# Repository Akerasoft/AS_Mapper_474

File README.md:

# AS_Mapper_474
NES compatible mapper that gives nearly 48KB instead of 32KB.  Has the linear space of NROM so no bank swapping.

Begining byte is $4020 until $FFFF.  Called NROM-383 by rounding down.
Mapper 474 submapper 0.

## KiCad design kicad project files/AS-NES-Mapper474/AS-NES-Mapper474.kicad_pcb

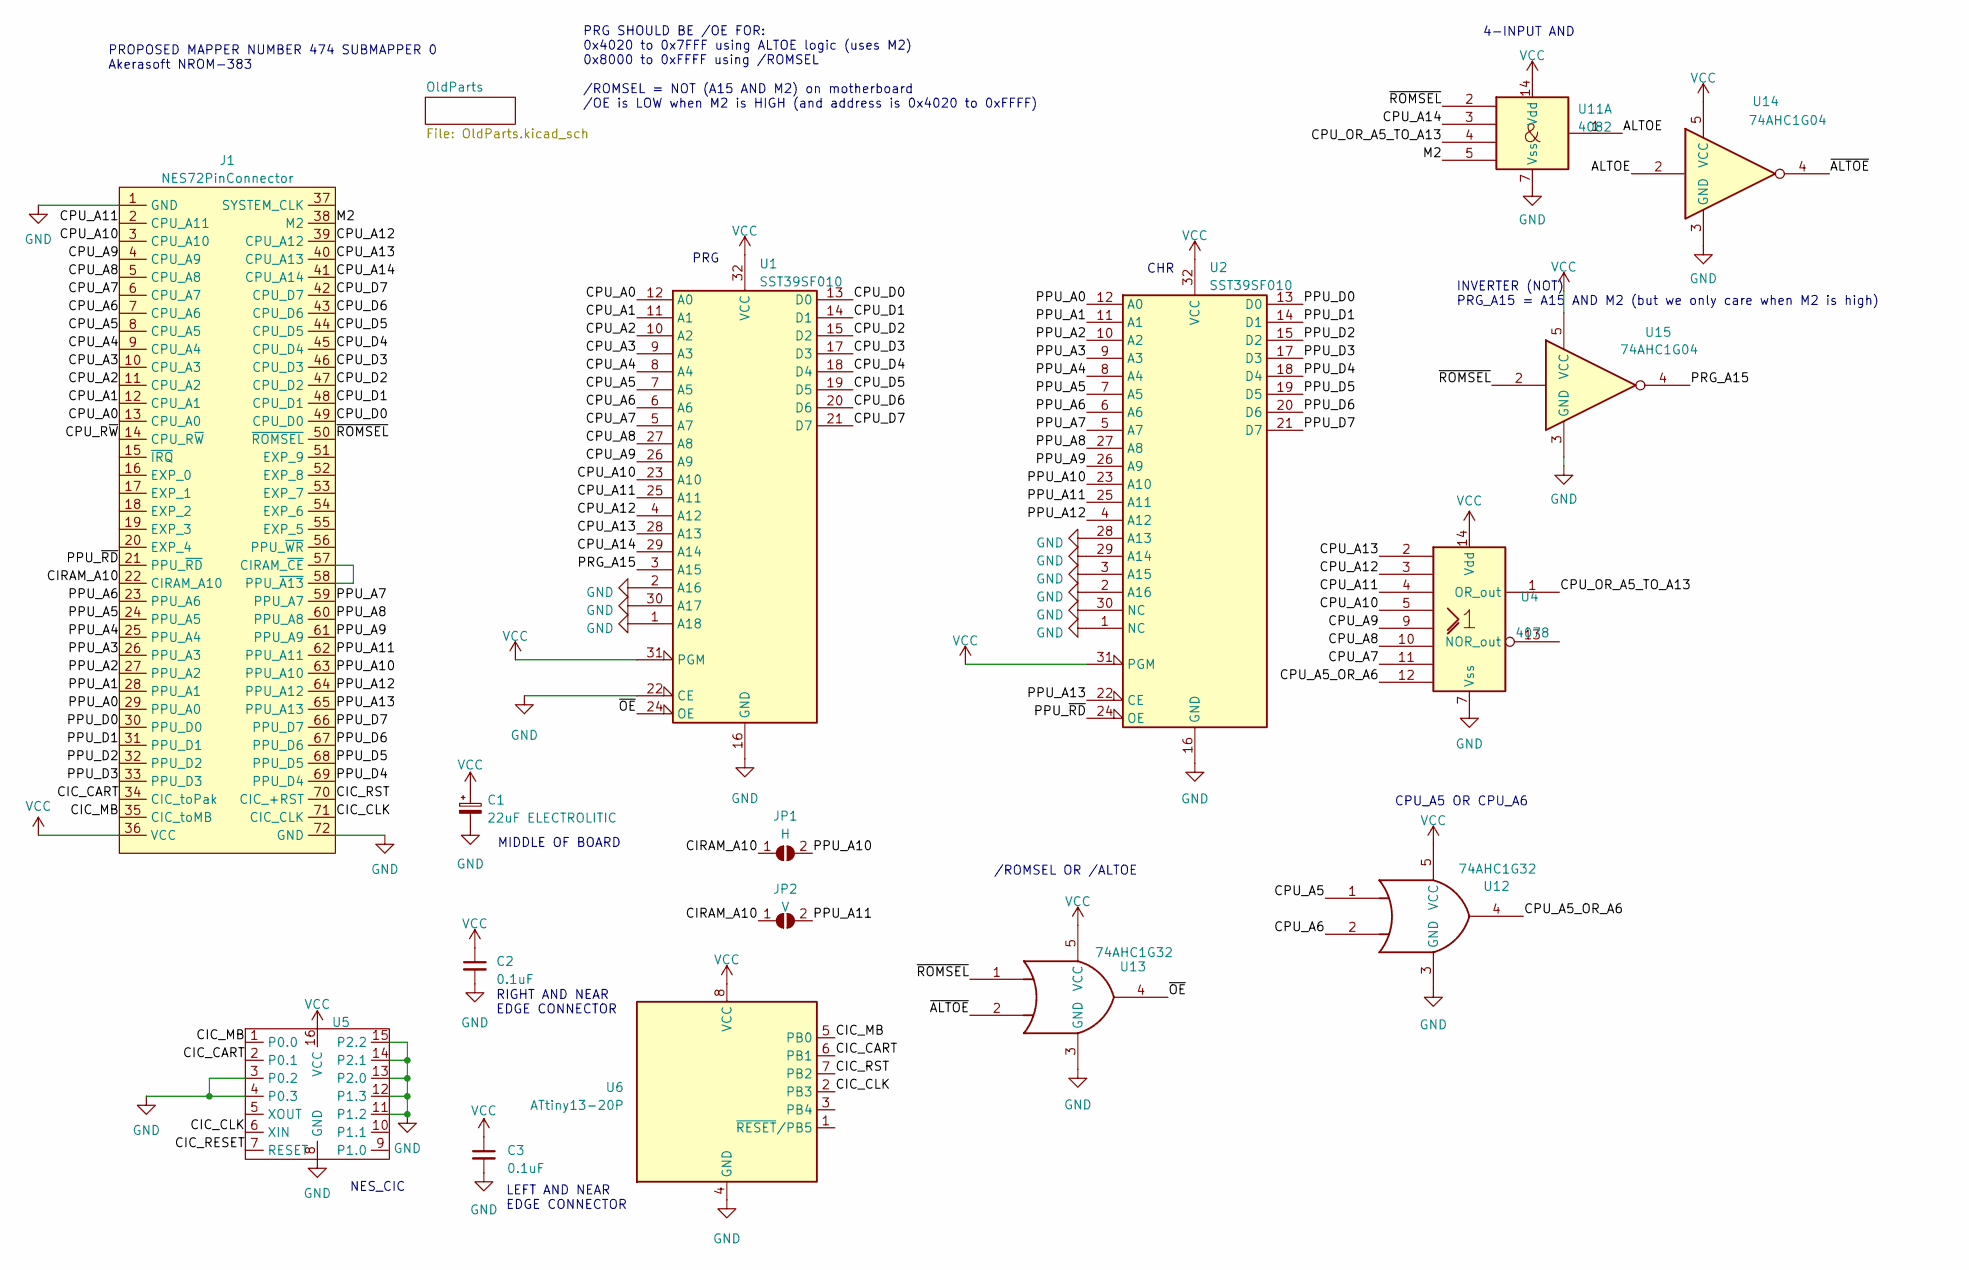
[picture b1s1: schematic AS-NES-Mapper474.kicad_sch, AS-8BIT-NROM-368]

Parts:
C1: 22uF ELECTROLITIC; CP_Radial_D5.0mm_P2.50mm
C2, C3: 0.1uF; C_Disc_D3.0mm_W1.6mm_P2.50mm
J1: NES72PinConnector; NES72PinEdgeConnector2
JP1: H; SolderJumper-2_P1.3mm_Open_Pad1.0x1.5mm
JP2: V; SolderJumper-2_P1.3mm_Open_Pad1.0x1.5mm
U1, U2: SST39SF010; DIP-32_W15.24mm
U4: 4078; DIP-14_W7.62mm
U5: DIP-16_W7.62mm
U6: ATtiny13-20P; DIP-8_W7.62mm
U11: 4082; DIP-14_W7.62mm
U12, U13: 74AHC1G32; SOT-23-5
U14, U15: 74AHC1G04; SOT-23-5

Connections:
/ALTOE: U11.1, U14.2
/CIC_CART: J1.34 (CIC_toPak), U5.2 (P0.1), U6.6 (PB1)
/CIC_CLK: J1.71 (CIC_CLK), U5.6 (XIN), U6.2 (PB3)
/CIC_MB: J1.35 (CIC_toMB), U5.1 (P0.0), U6.5 (PB0)
/CIC_RESET: U5.7 (RESET)
/CIC_RST: J1.70 (CIC_+RST), U6.7 (PB2)
/CIRAM_A10: J1.22 (CIRAM_A10), JP1.1 (A), JP2.1 (A)
/CPU_A0: J1.13 (CPU_A0), U1.12 (A0)
/CPU_A1: J1.12 (CPU_A1), U1.11 (A1)
/CPU_A2: J1.11 (CPU_A2), U1.10 (A2)
/CPU_A3: J1.10 (CPU_A3), U1.9 (A3)
/CPU_A4: J1.9 (CPU_A4), U1.8 (A4)
/CPU_A5: J1.8 (CPU_A5), U1.7 (A5), U12.1
/CPU_A5_OR_A6: U4.12, U12.4
/CPU_A6: J1.7 (CPU_A6), U1.6 (A6), U12.2
/CPU_A7: J1.6 (CPU_A7), U1.5 (A7), U4.11
/CPU_A8: J1.5 (CPU_A8), U1.27 (A8), U4.10
/CPU_A9: J1.4 (CPU_A9), U1.26 (A9), U4.9
/CPU_A10: J1.3 (CPU_A10), U1.23 (A10), U4.5
/CPU_A11: J1.2 (CPU_A11), U1.25 (A11), U4.4
/CPU_A12: J1.39 (CPU_A12), U1.4 (A12), U4.3
/CPU_A13: J1.40 (CPU_A13), U1.28 (A13), U4.2
/CPU_A14: J1.41 (CPU_A14), U1.29 (A14), U11.3
/CPU_D0: J1.49 (CPU_D0), U1.13 (D0)
/CPU_D1: J1.48 (CPU_D1), U1.14 (D1)
/CPU_D2: J1.47 (CPU_D2), U1.15 (D2)
/CPU_D3: J1.46 (CPU_D3), U1.17 (D3)
/CPU_D4: J1.45 (CPU_D4), U1.18 (D4)
/CPU_D5: J1.44 (CPU_D5), U1.19 (D5)
/CPU_D6: J1.43 (CPU_D6), U1.20 (D6)
/CPU_D7: J1.42 (CPU_D7), U1.21 (D7)
/CPU_OR_A5_TO_A13: U4.1 (OR_out), U11.4
/CPU_R~W: J1.14 (CPU_R~W)
/M2: J1.38 (M2), U11.5
/PPU_A0: J1.29 (PPU_A0), U2.12 (A0)
/PPU_A1: J1.28 (PPU_A1), U2.11 (A1)
/PPU_A2: J1.27 (PPU_A2), U2.10 (A2)
/PPU_A3: J1.26 (PPU_A3), U2.9 (A3)
/PPU_A4: J1.25 (PPU_A4), U2.8 (A4)
/PPU_A5: J1.24 (PPU_A5), U2.7 (A5)
/PPU_A6: J1.23 (PPU_A6), U2.6 (A6)
/PPU_A7: J1.59 (PPU_A7), U2.5 (A7)
/PPU_A8: J1.60 (PPU_A8), U2.27 (A8)
/PPU_A9: J1.61 (PPU_A9), U2.26 (A9)
/PPU_A10: J1.63 (PPU_A10), JP1.2 (B), U2.23 (A10)
/PPU_A11: J1.62 (PPU_A11), JP2.2 (B), U2.25 (A11)
/PPU_A12: J1.64 (PPU_A12), U2.4 (A12)
/PPU_A13: J1.65 (PPU_A13), U2.22 (CE)
/PPU_D0: J1.30 (PPU_D0), U2.13 (D0)
/PPU_D1: J1.31 (PPU_D1), U2.14 (D1)
/PPU_D2: J1.32 (PPU_D2), U2.15 (D2)
/PPU_D3: J1.33 (PPU_D3), U2.17 (D3)
/PPU_D4: J1.69 (PPU_D4), U2.18 (D4)
/PPU_D5: J1.68 (PPU_D5), U2.19 (D5)
/PPU_D6: J1.67 (PPU_D6), U2.20 (D6)
/PPU_D7: J1.66 (PPU_D7), U2.21 (D7)
/PPU_~RD: J1.21 (PPU_~RD), U2.24 (OE)
/PRG_A15: U1.3 (A15), U15.4
/~ALTOE: U13.2, U14.4
/~OE: U1.24 (OE), U13.4
/~ROMSEL: J1.50 (~ROMSEL), U11.2, U13.1, U15.2
GND: C1.2, C2.2, C3.2, J1.1 (GND), J1.72 (GND), U1.1 (A18), U1.2 (A16), U1.16 (GND), U1.22 (CE), U1.30 (A17), U2.1 (NC), U2.2 (A16), U2.3 (A15), U2.16 (GND), U2.28 (A13), U2.29 (A14), U2.30 (NC), U4.7 (Vss), U5.3 (P0.2), U5.4 (P0.3), U5.8 (GND), U5.11 (P1.2), U5.12 (P1.3), U5.13 (P2.0), U5.14 (P2.1), U5.15 (P2.2), U6.4 (GND), U11.7 (Vss), U12.3 (GND), U13.3 (GND), U14.3 (GND), U15.3 (GND)
unnamed: J1.57 (CIRAM_~CE), J1.58 (PPU_~A13)
VCC: C1.1, C2.1, C3.1, J1.36 (VCC), U1.31 (PGM), U1.32 (VCC), U2.31 (PGM), U2.32 (VCC), U4.14 (Vdd), U5.16 (VCC), U6.8 (VCC), U11.14 (Vdd), U12.5 (VCC), U13.5 (VCC), U14.5 (VCC), U15.5 (VCC)

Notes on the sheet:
PROPOSED MAPPER NUMBER 474 SUBMAPPER 0 Akerasoft NROM-383
4-INPUT AND
/ROMSEL OR /ALTOE
RIGHT AND NEAR EDGE CONNECTOR
PRG SHOULD BE /OE FOR: 0x4020 to 0x7FFF using ALTOE logic (uses M2) 0x8000 to 0xFFFF using /ROMSEL /ROMSEL = NOT (A15 AND M2) on motherboard /OE is LOW when M2 is HIGH (and address is 0x4020 to 0xFFFF)
INVERTER (NOT) PRG_A15 = A15 AND M2 (but we only care when M2 is high)
CHR
MIDDLE OF BOARD
LEFT AND NEAR EDGE CONNECTOR
NES_CIC
PRG
CPU_A5 OR CPU_A6

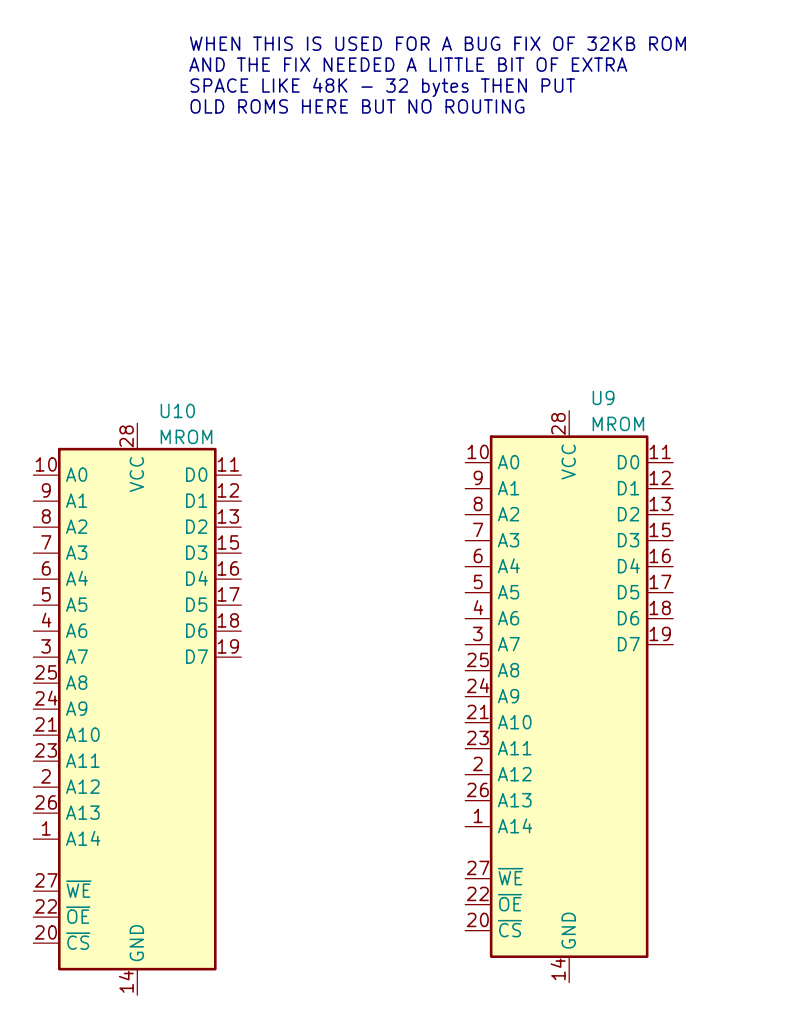
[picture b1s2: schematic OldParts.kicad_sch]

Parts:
U9, U10: MROM; DIP-28_W15.24mm

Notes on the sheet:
WHEN THIS IS USED FOR A BUG FIX OF 32KB ROM AND THE FIX NEEDED A LITTLE BIT OF EXTRA SPACE LIKE 48K - 32 bytes THEN PUT OLD ROMS HERE BUT NO ROUTING

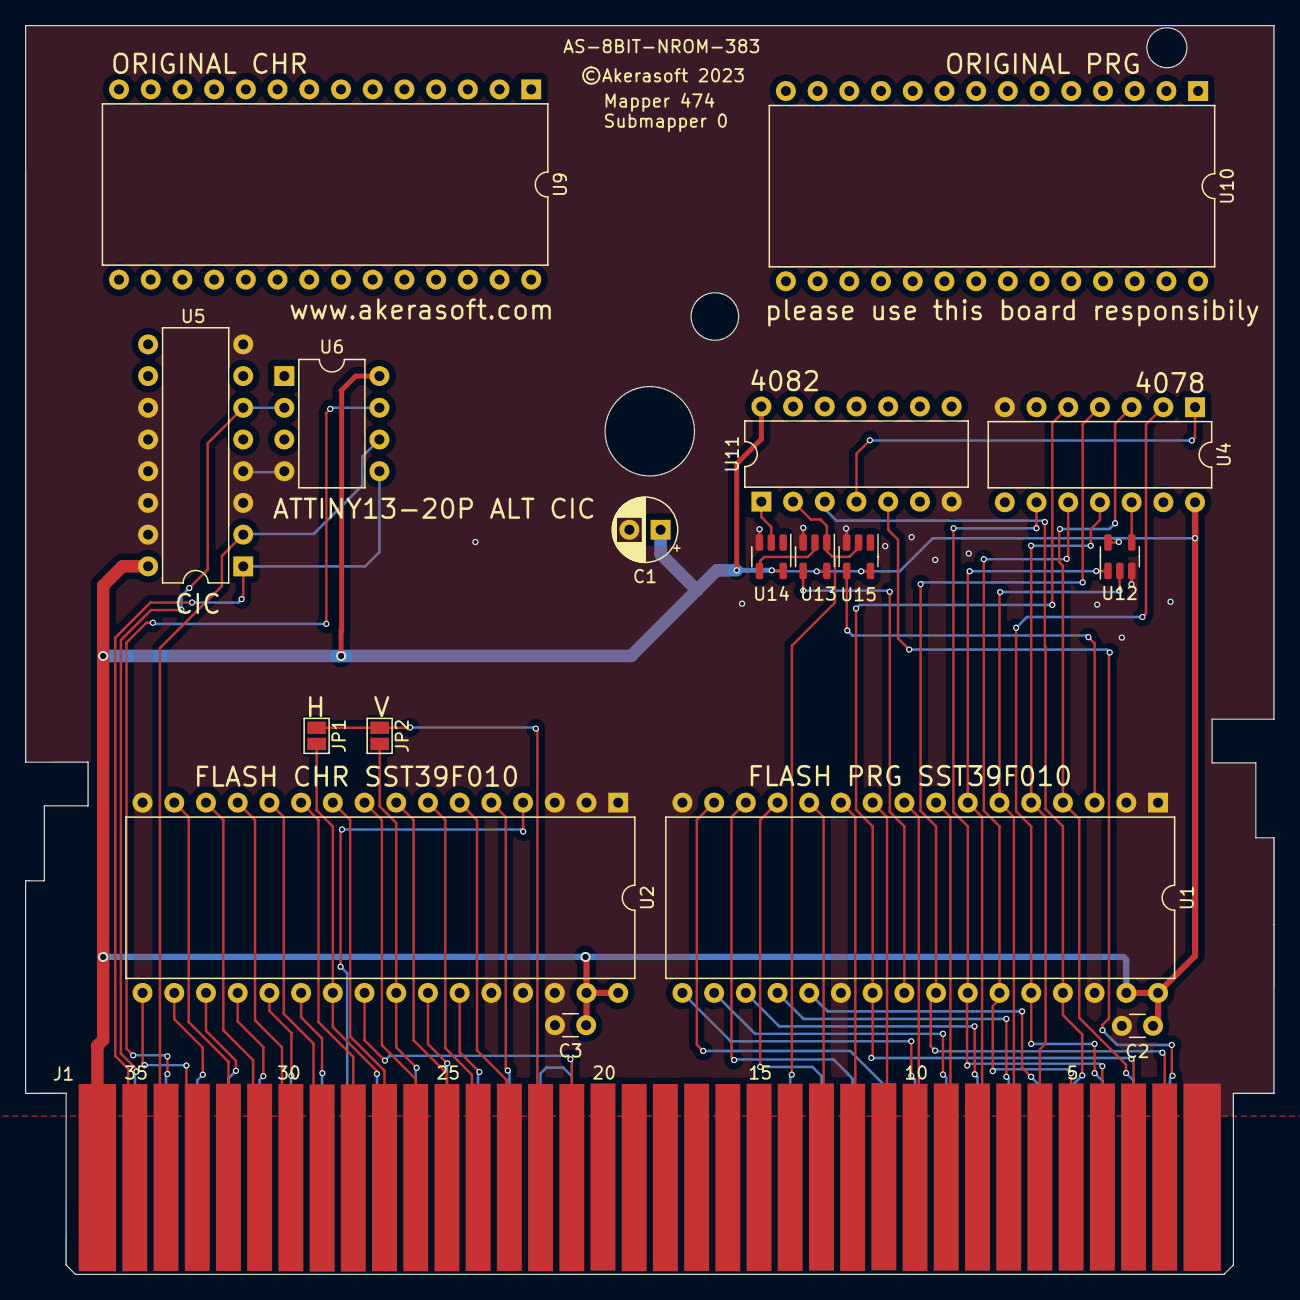
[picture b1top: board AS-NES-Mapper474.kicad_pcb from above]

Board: 2 copper layers, 100.0 x 100.0 mm, 18 parts (0 on the bottom side), 62 nets.

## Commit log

2023-06-27 Cleanup
2023-06-27 Add Bill of Materials (BOM)
2023-06-27 Update pictures

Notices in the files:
kicad project files/AS-NES-Mapper474/AS-NES-Mapper474.kicad_pcb:
©Akerasoft 2023
kicad project files/AS-NES-Mapper474/AS-NES-Mapper474.kicad_sch:
©Akerasoft
